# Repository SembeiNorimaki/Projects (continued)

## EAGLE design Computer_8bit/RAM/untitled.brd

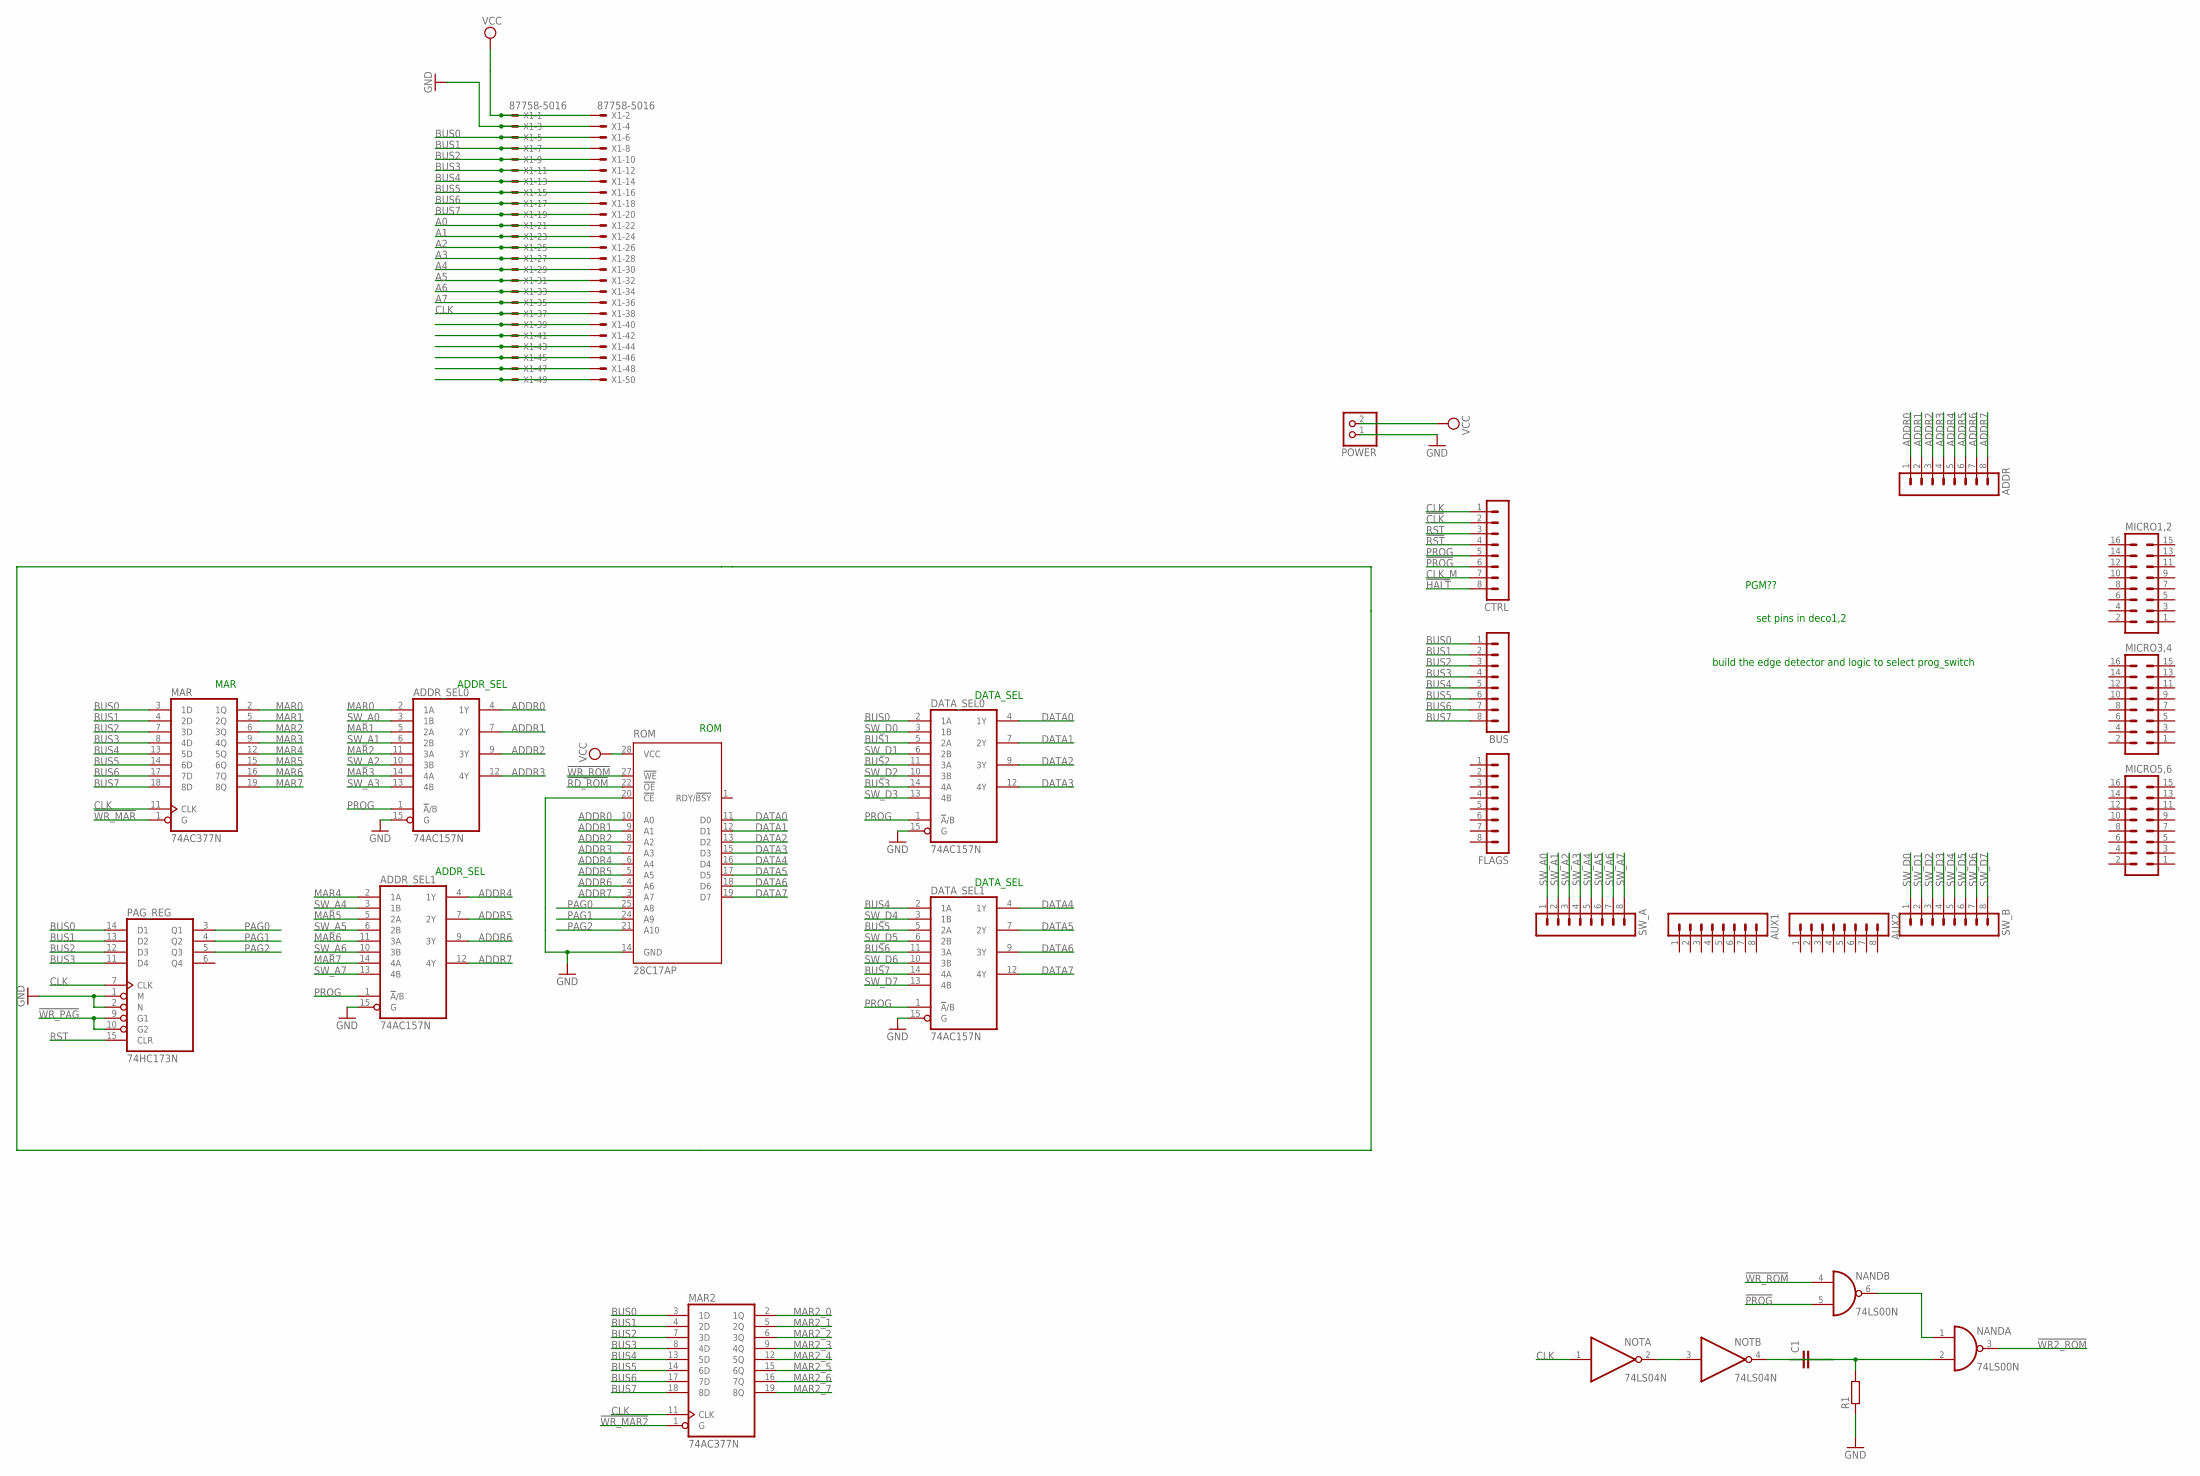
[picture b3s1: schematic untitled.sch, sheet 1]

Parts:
ADDR: MA08-1
ADDR_SEL0, ADDR_SEL1: 74AC157N; DIL16
AUX1, AUX2: MA08-1
BUS: MA08-1
C1: C2.5/4; C2.5-4
CTRL: MA08-1
DATA_SEL0, DATA_SEL1: 74AC157N; DIL16
FLAGS: MA08-1
MAR, MAR2: 74AC377N; DIL20
MICRO1,2, MICRO3,4, MICRO5,6: MA08-2
NAND: 74LS00N; DIL14
NOT: 74LS04N; DIL14
PAG_REG: 74HC173N; DIL16
POWER: PINHD-1X2; 1X02
R1: R0207/10; 0207/10
ROM: 28C17AP; DIL28-6
SW_A: MA08-1
SW_B: MA08-1
X1: 87758-5016

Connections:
!CLK: CTRL.2
!HALT: CTRL.8
!PROG: CTRL.6, NAND.5 (I1)
!RD_ROM: ROM.22 (!OE)
!RST: CTRL.4
!WR2_ROM: NAND.3 (O)
!WR_MAR: MAR.1 (G)
!WR_MAR2: MAR2.1 (G)
!WR_PAG: PAG_REG.9 (G1), PAG_REG.10 (G2)
!WR_ROM: NAND.4 (I0), ROM.27 (!WE)
A0: X1.21, X1.22
A1: X1.23, X1.24
A2: X1.25, X1.26
A3: X1.27, X1.28
A4: X1.29, X1.30
A5: X1.31, X1.32
A6: X1.33, X1.34
A7: X1.35, X1.36
ADDR0: ADDR.1, ADDR_SEL0.4 (1Y), ROM.10 (A0)
ADDR1: ADDR.2, ADDR_SEL0.7 (2Y), ROM.9 (A1)
ADDR2: ADDR.3, ADDR_SEL0.9 (3Y), ROM.8 (A2)
ADDR3: ADDR.4, ADDR_SEL0.12 (4Y), ROM.7 (A3)
ADDR4: ADDR.5, ADDR_SEL1.4 (1Y), ROM.6 (A4)
ADDR5: ADDR.6, ADDR_SEL1.7 (2Y), ROM.5 (A5)
ADDR6: ADDR.7, ADDR_SEL1.9 (3Y), ROM.4 (A6)
ADDR7: ADDR.8, ADDR_SEL1.12 (4Y), ROM.3 (A7)
BUS0: BUS.1, DATA_SEL0.2 (1A), MAR.3 (1D), MAR2.3 (1D), PAG_REG.14 (D1), X1.5, X1.6
BUS1: BUS.2, DATA_SEL0.5 (2A), MAR.4 (2D), MAR2.4 (2D), PAG_REG.13 (D2), X1.7, X1.8
BUS2: BUS.3, DATA_SEL0.11 (3A), MAR.7 (3D), MAR2.7 (3D), PAG_REG.12 (D3), X1.9, X1.10
BUS3: BUS.4, DATA_SEL0.14 (4A), MAR.8 (4D), MAR2.8 (4D), PAG_REG.11 (D4), X1.11, X1.12
BUS4: BUS.5, DATA_SEL1.2 (1A), MAR.13 (5D), MAR2.13 (5D), X1.13, X1.14
BUS5: BUS.6, DATA_SEL1.5 (2A), MAR.14 (6D), MAR2.14 (6D), X1.15, X1.16
BUS6: BUS.7, DATA_SEL1.11 (3A), MAR.17 (7D), MAR2.17 (7D), X1.17, X1.18
BUS7: BUS.8, DATA_SEL1.14 (4A), MAR.18 (8D), MAR2.18 (8D), X1.19, X1.20
CLK: CTRL.1, MAR.11 (CLK), MAR2.11 (CLK), NOT.1 (I), PAG_REG.7 (CLK), X1.37, X1.38
CLK_M: CTRL.7
DATA0: DATA_SEL0.4 (1Y), ROM.11 (D0)
DATA1: DATA_SEL0.7 (2Y), ROM.12 (D1)
DATA2: DATA_SEL0.9 (3Y), ROM.13 (D2)
DATA3: DATA_SEL0.12 (4Y), ROM.15 (D3)
DATA4: DATA_SEL1.4 (1Y), ROM.16 (D4)
DATA5: DATA_SEL1.7 (2Y), ROM.17 (D5)
DATA6: DATA_SEL1.9 (3Y), ROM.18 (D6)
DATA7: DATA_SEL1.12 (4Y), ROM.19 (D7)
GND: ADDR_SEL0.8 (GND), ADDR_SEL0.15 (G), ADDR_SEL1.8 (GND), ADDR_SEL1.15 (G), DATA_SEL0.8 (GND), DATA_SEL0.15 (G), DATA_SEL1.8 (GND), DATA_SEL1.15 (G), MAR.10 (GND), MAR2.10 (GND), NAND.7 (GND), NOT.7 (GND), PAG_REG.1 (M), PAG_REG.2 (N), PAG_REG.8 (GND), POWER.1, R1.1, ROM.14 (GND), ROM.20 (!CE), X1.3, X1.4
MAR0: ADDR_SEL0.2 (1A), MAR.2 (1Q)
MAR1: ADDR_SEL0.5 (2A), MAR.5 (2Q)
MAR2: ADDR_SEL0.11 (3A), MAR.6 (3Q)
MAR2_0: MAR2.2 (1Q)
MAR2_1: MAR2.5 (2Q)
MAR2_2: MAR2.6 (3Q)
MAR2_3: MAR2.9 (4Q)
MAR2_4: MAR2.12 (5Q)
MAR2_5: MAR2.15 (6Q)
MAR2_6: MAR2.16 (7Q)
MAR2_7: MAR2.19 (8Q)
MAR3: ADDR_SEL0.14 (4A), MAR.9 (4Q)
MAR4: ADDR_SEL1.2 (1A), MAR.12 (5Q)
MAR5: ADDR_SEL1.5 (2A), MAR.15 (6Q)
MAR6: ADDR_SEL1.11 (3A), MAR.16 (7Q)
MAR7: ADDR_SEL1.14 (4A), MAR.19 (8Q)
unnamed: X1.49, X1.50
unnamed: NOT.2 (O), NOT.3 (I)
unnamed: C1.2, NAND.2 (I1), R1.2
unnamed: C1.1, NOT.4 (O)
unnamed: NAND.1 (I0), NAND.6 (O)
unnamed: X1.39, X1.40
unnamed: X1.41, X1.42
unnamed: X1.43, X1.44
unnamed: X1.45, X1.46
unnamed: X1.47, X1.48
PAG0: PAG_REG.3 (Q1), ROM.25 (A8)
PAG1: PAG_REG.4 (Q2), ROM.24 (A9)
PAG2: PAG_REG.5 (Q3), ROM.21 (A10)
PROG: ADDR_SEL0.1 (!A!/B), ADDR_SEL1.1 (!A!/B), CTRL.5, DATA_SEL0.1 (!A!/B), DATA_SEL1.1 (!A!/B)
RST: CTRL.3, PAG_REG.15 (CLR)
SW_A0: ADDR_SEL0.3 (1B), SW_A.1
SW_A1: ADDR_SEL0.6 (2B), SW_A.2
SW_A2: ADDR_SEL0.10 (3B), SW_A.3
SW_A3: ADDR_SEL0.13 (4B), SW_A.4
SW_A4: ADDR_SEL1.3 (1B), SW_A.5
SW_A5: ADDR_SEL1.6 (2B), SW_A.6
SW_A6: ADDR_SEL1.10 (3B), SW_A.7
SW_A7: ADDR_SEL1.13 (4B), SW_A.8
SW_D0: DATA_SEL0.3 (1B), SW_B.1
SW_D1: DATA_SEL0.6 (2B), SW_B.2
SW_D2: DATA_SEL0.10 (3B), SW_B.3
SW_D3: DATA_SEL0.13 (4B), SW_B.4
SW_D4: DATA_SEL1.3 (1B), SW_B.5
SW_D5: DATA_SEL1.6 (2B), SW_B.6
SW_D6: DATA_SEL1.10 (3B), SW_B.7
SW_D7: DATA_SEL1.13 (4B), SW_B.8
VCC: ADDR_SEL0.16 (VCC), ADDR_SEL1.16 (VCC), DATA_SEL0.16 (VCC), DATA_SEL1.16 (VCC), MAR.20 (VCC), MAR2.20 (VCC), NAND.14 (VCC), NOT.14 (VCC), PAG_REG.16 (VCC), POWER.2, ROM.28 (VCC), X1.1, X1.2

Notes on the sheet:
ROM
MAR
ADDR_SEL
DATA_SEL
PGM??
set pins in deco1,2
build the edge detector and logic to select prog_switch

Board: 2 copper layers, 25 parts (0 on the bottom side), 77 nets, no tracks yet.

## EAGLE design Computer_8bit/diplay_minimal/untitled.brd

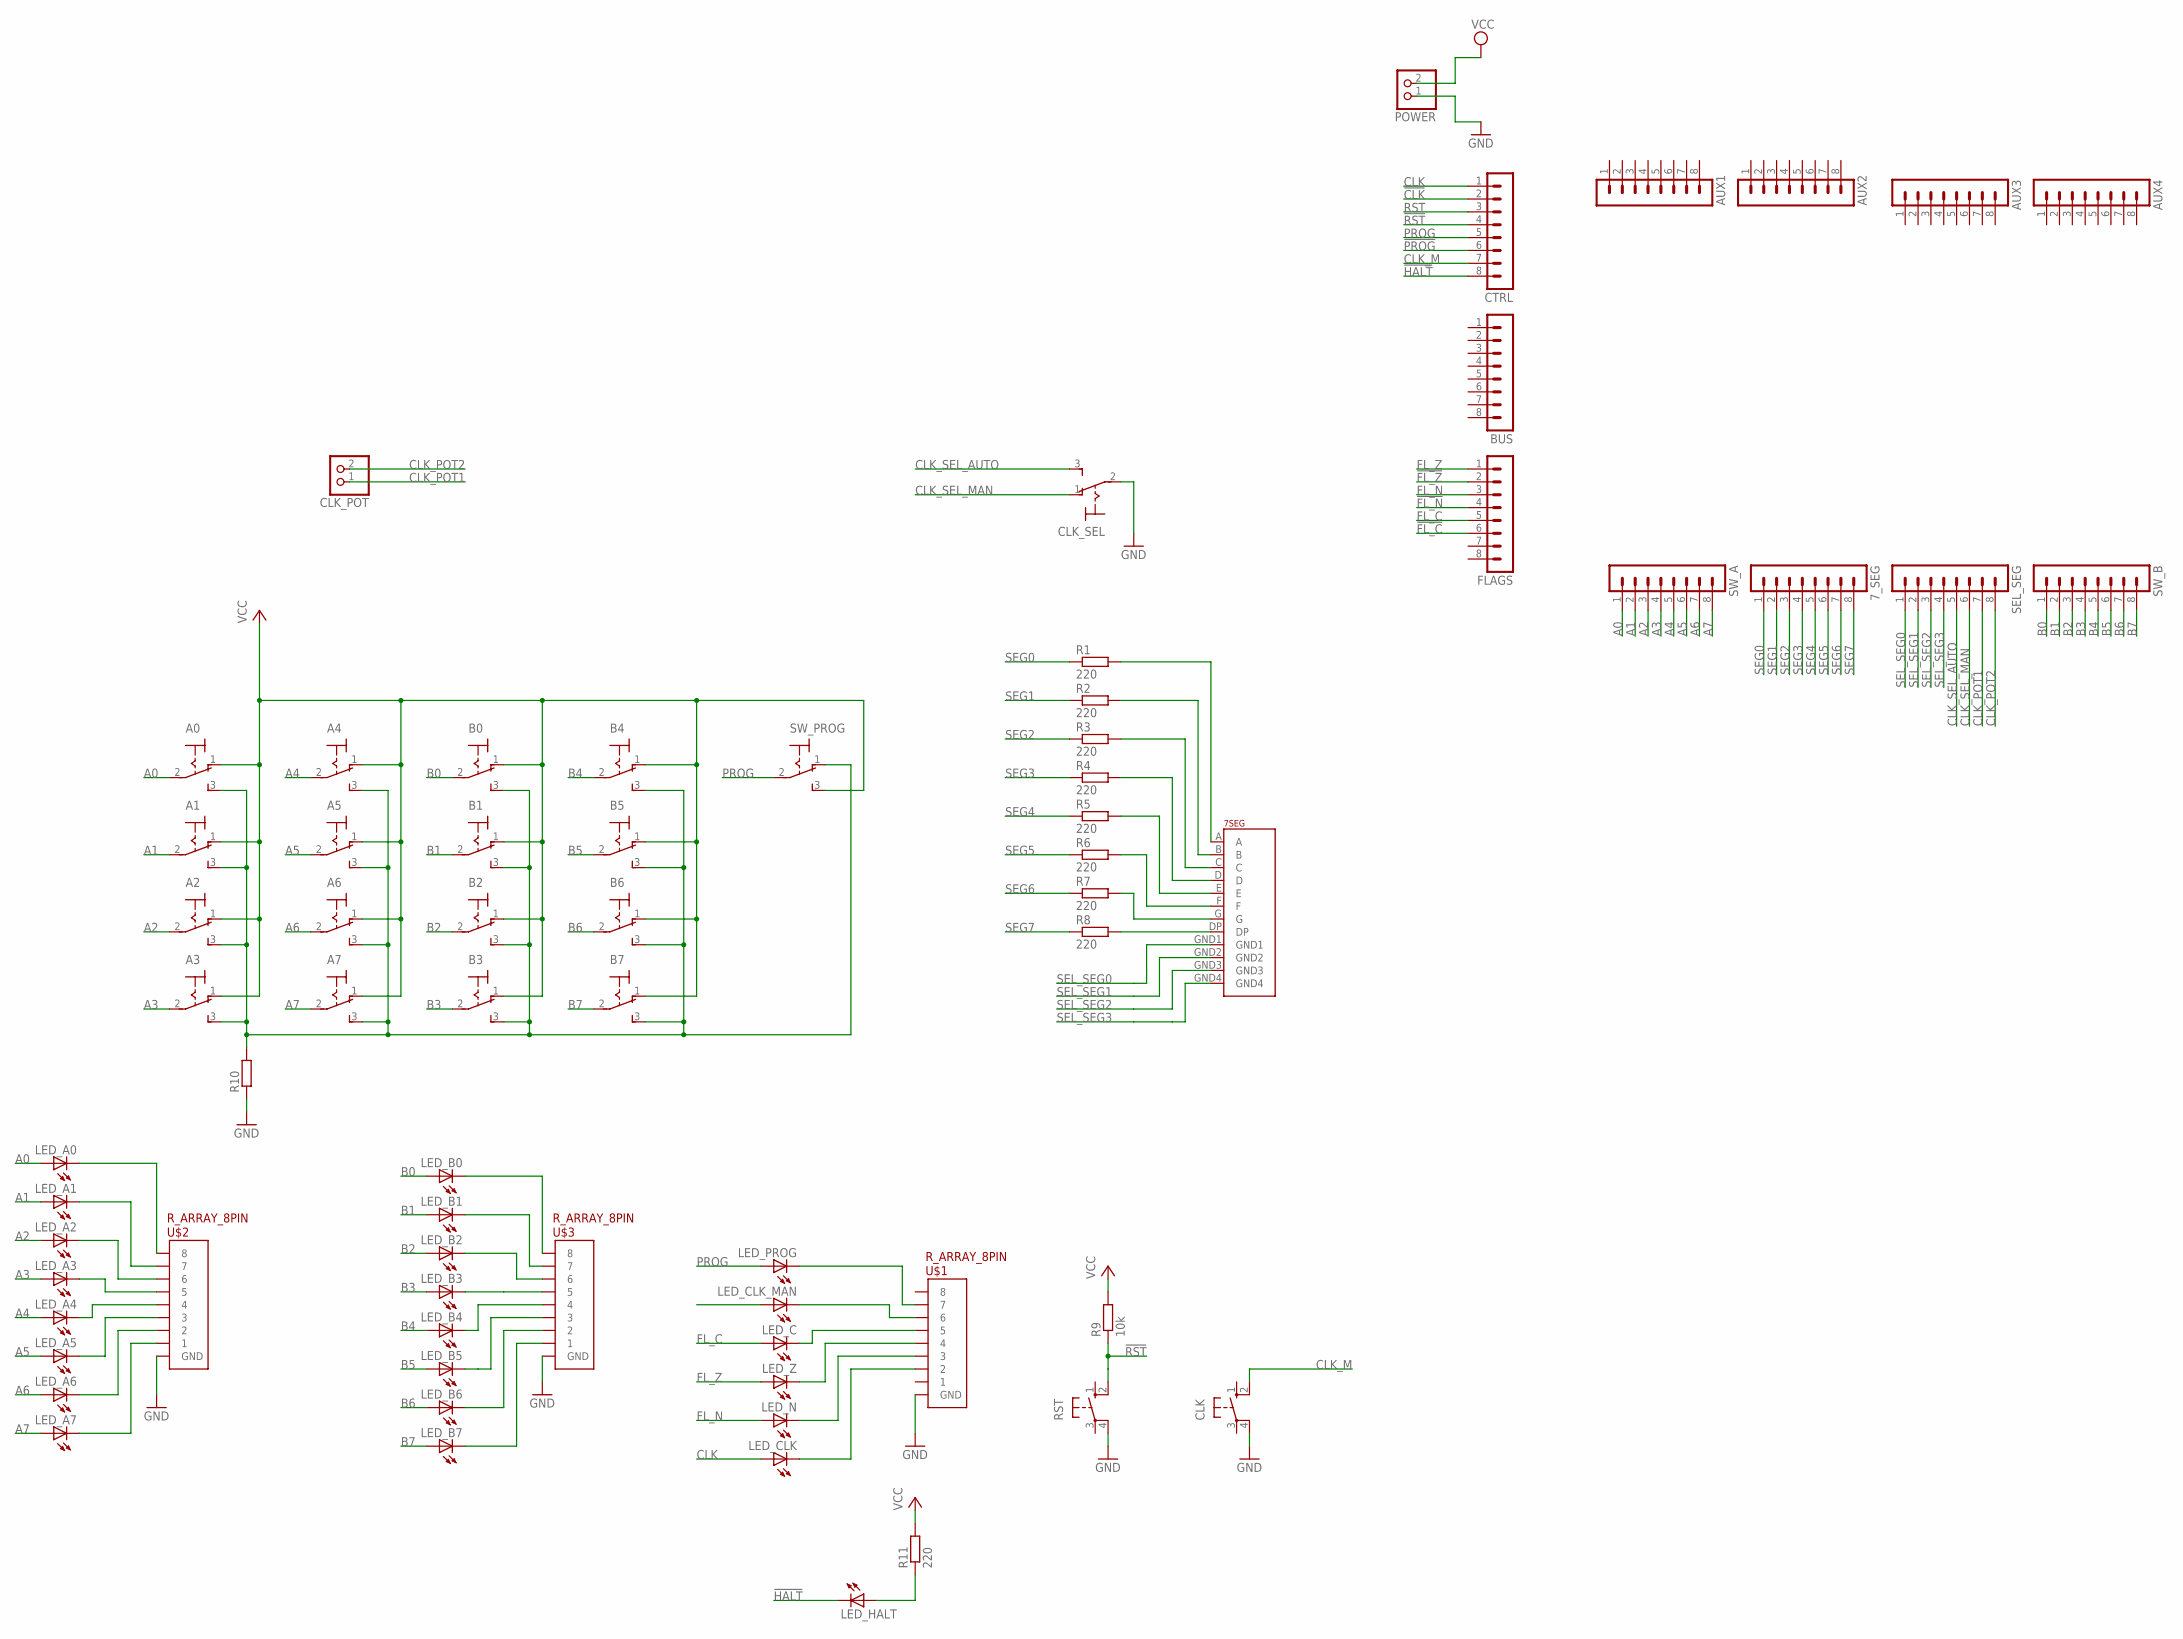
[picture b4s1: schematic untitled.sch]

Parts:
7SEG: 7SEGX4
7_SEG: MA08-1
A0, A1, A2, A3, A4, A5, A6, A7: M9040P
AUX1, AUX2, AUX3, AUX4: MA08-1
B0, B1, B2, B3, B4, B5, B6, B7: M9040P
BUS: MA08-1
CLK: 10-XX; B3F-10XX
CLK_POT: PINHD-1X2; 1X02
CLK_SEL: M9040P
CTRL: MA08-1
FLAGS: MA08-1
LED_A0, LED_A1, LED_A2, LED_A3, LED_A4, LED_A5, LED_A6, LED_A7: LED3MM
LED_B0, LED_B1, LED_B2, LED_B3, LED_B4, LED_B5, LED_B6, LED_B7: LED3MM
LED_C: LED3MM
LED_CLK: LED3MM
LED_CLK_MAN: LED3MM
LED_HALT: LED3MM
LED_N: LED3MM
LED_PROG: LED3MM
LED_Z: LED3MM
POWER: PINHD-1X2; 1X02
R1, R2, R3, R4, R5, R6, R7, R8, R11: 220; 0207/10
R9: 10k; 0207/10
R10: R0207/10; 0207/10
RST: 10-XX; B3F-10XX
SEL_SEG: MA08-1
SW_A: MA08-1
SW_B: MA08-1
SW_PROG: M9040P
U$1, U$2, U$3: R_ARRAY_8PIN

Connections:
!CLK: CTRL.2
!FL_C: FLAGS.6
!FL_N: FLAGS.4
!FL_Z: FLAGS.2
!HALT: CTRL.8, LED_HALT.K (C)
!PROG: CTRL.6
!RST: CTRL.4, R9.1, RST.2 (S1)
A0: A0.2, LED_A0.A, SW_A.1
A1: A1.2, LED_A1.A, SW_A.2
A2: A2.2, LED_A2.A, SW_A.3
A3: A3.2, LED_A3.A, SW_A.4
A4: A4.2, LED_A4.A, SW_A.5
A5: A5.2, LED_A5.A, SW_A.6
A6: A6.2, LED_A6.A, SW_A.7
A7: A7.2, LED_A7.A, SW_A.8
B0: B0.2, LED_B0.A, SW_B.1
B1: B1.2, LED_B1.A, SW_B.2
B2: B2.2, LED_B2.A, SW_B.3
B3: B3.2, LED_B3.A, SW_B.4
B4: B4.2, LED_B4.A, SW_B.5
B5: B5.2, LED_B5.A, SW_B.6
B6: B6.2, LED_B6.A, SW_B.7
B7: B7.2, LED_B7.A, SW_B.8
CLK: CTRL.1, LED_CLK.A
CLK_M: CLK.2 (S1), CTRL.7
CLK_POT1: CLK_POT.1, SEL_SEG.7
CLK_POT2: CLK_POT.2, SEL_SEG.8
CLK_SEL_AUTO: CLK_SEL.3 (S), SEL_SEG.5
CLK_SEL_MAN: CLK_SEL.1 (O), SEL_SEG.6
FL_C: FLAGS.5, LED_C.A
FL_N: FLAGS.3, LED_N.A
FL_Z: FLAGS.1, LED_Z.A
GND: CLK.4 (P1), CLK_SEL.2, POWER.1, R10.1, RST.4 (P1), U$1.GND, U$2.GND, U$3.GND
unnamed: LED_A0.K (C), U$2.8
unnamed: A0.3 (S), A1.3 (S), A2.3 (S), A3.3 (S), A4.3 (S), A5.3 (S), A6.3 (S), A7.3 (S), B0.3 (S), B1.3 (S), B2.3 (S), B3.3 (S), B4.3 (S), B5.3 (S), B6.3 (S), B7.3 (S), R10.2, SW_PROG.1 (O)
unnamed: 7SEG.A, R1.2
unnamed: LED_HALT.A, R11.1
unnamed: 7SEG.B, R2.2
unnamed: 7SEG.C, R3.2
unnamed: 7SEG.D, R4.2
unnamed: 7SEG.E, R5.2
unnamed: 7SEG.F, R6.2
unnamed: 7SEG.G, R7.2
unnamed: 7SEG.DP, R8.2
unnamed: LED_A1.K (C), U$2.7
unnamed: LED_A2.K (C), U$2.6
unnamed: LED_A3.K (C), U$2.5
unnamed: LED_A4.K (C), U$2.4
unnamed: LED_A5.K (C), U$2.3
unnamed: LED_A6.K (C), U$2.2
unnamed: LED_A7.K (C), U$2.1
unnamed: LED_B0.K (C), U$3.8
unnamed: LED_B1.K (C), U$3.7
unnamed: LED_B2.K (C), U$3.6
unnamed: LED_B3.K (C), U$3.5
unnamed: LED_B4.K (C), U$3.4
unnamed: LED_B5.K (C), U$3.3
unnamed: LED_B6.K (C), U$3.2
unnamed: LED_B7.K (C), U$3.1
unnamed: LED_PROG.K (C), U$1.7
unnamed: LED_CLK_MAN.K (C), U$1.6
unnamed: LED_C.K (C), U$1.5
unnamed: LED_Z.K (C), U$1.4
unnamed: LED_N.K (C), U$1.3
unnamed: LED_CLK.K (C), U$1.2
PROG: CTRL.5, LED_PROG.A, SW_PROG.2
RST: CTRL.3
SEG0: 7_SEG.1, R1.1
SEG1: 7_SEG.2, R2.1
SEG2: 7_SEG.3, R3.1
SEG3: 7_SEG.4, R4.1
SEG4: 7_SEG.5, R5.1
SEG5: 7_SEG.6, R6.1
SEG6: 7_SEG.7, R7.1
SEG7: 7_SEG.8, R8.1
SEL_SEG0: 7SEG.GND1, SEL_SEG.1
SEL_SEG1: 7SEG.GND2, SEL_SEG.2
SEL_SEG2: 7SEG.GND3, SEL_SEG.3
SEL_SEG3: 7SEG.GND4, SEL_SEG.4
VCC: A0.1 (O), A1.1 (O), A2.1 (O), A3.1 (O), A4.1 (O), A5.1 (O), A6.1 (O), A7.1 (O), B0.1 (O), B1.1 (O), B2.1 (O), B3.1 (O), B4.1 (O), B5.1 (O), B6.1 (O), B7.1 (O), POWER.2, R9.2, R11.2, SW_PROG.3 (S)

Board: 2 copper layers, 71 parts (0 on the bottom side), 74 nets, no tracks yet.

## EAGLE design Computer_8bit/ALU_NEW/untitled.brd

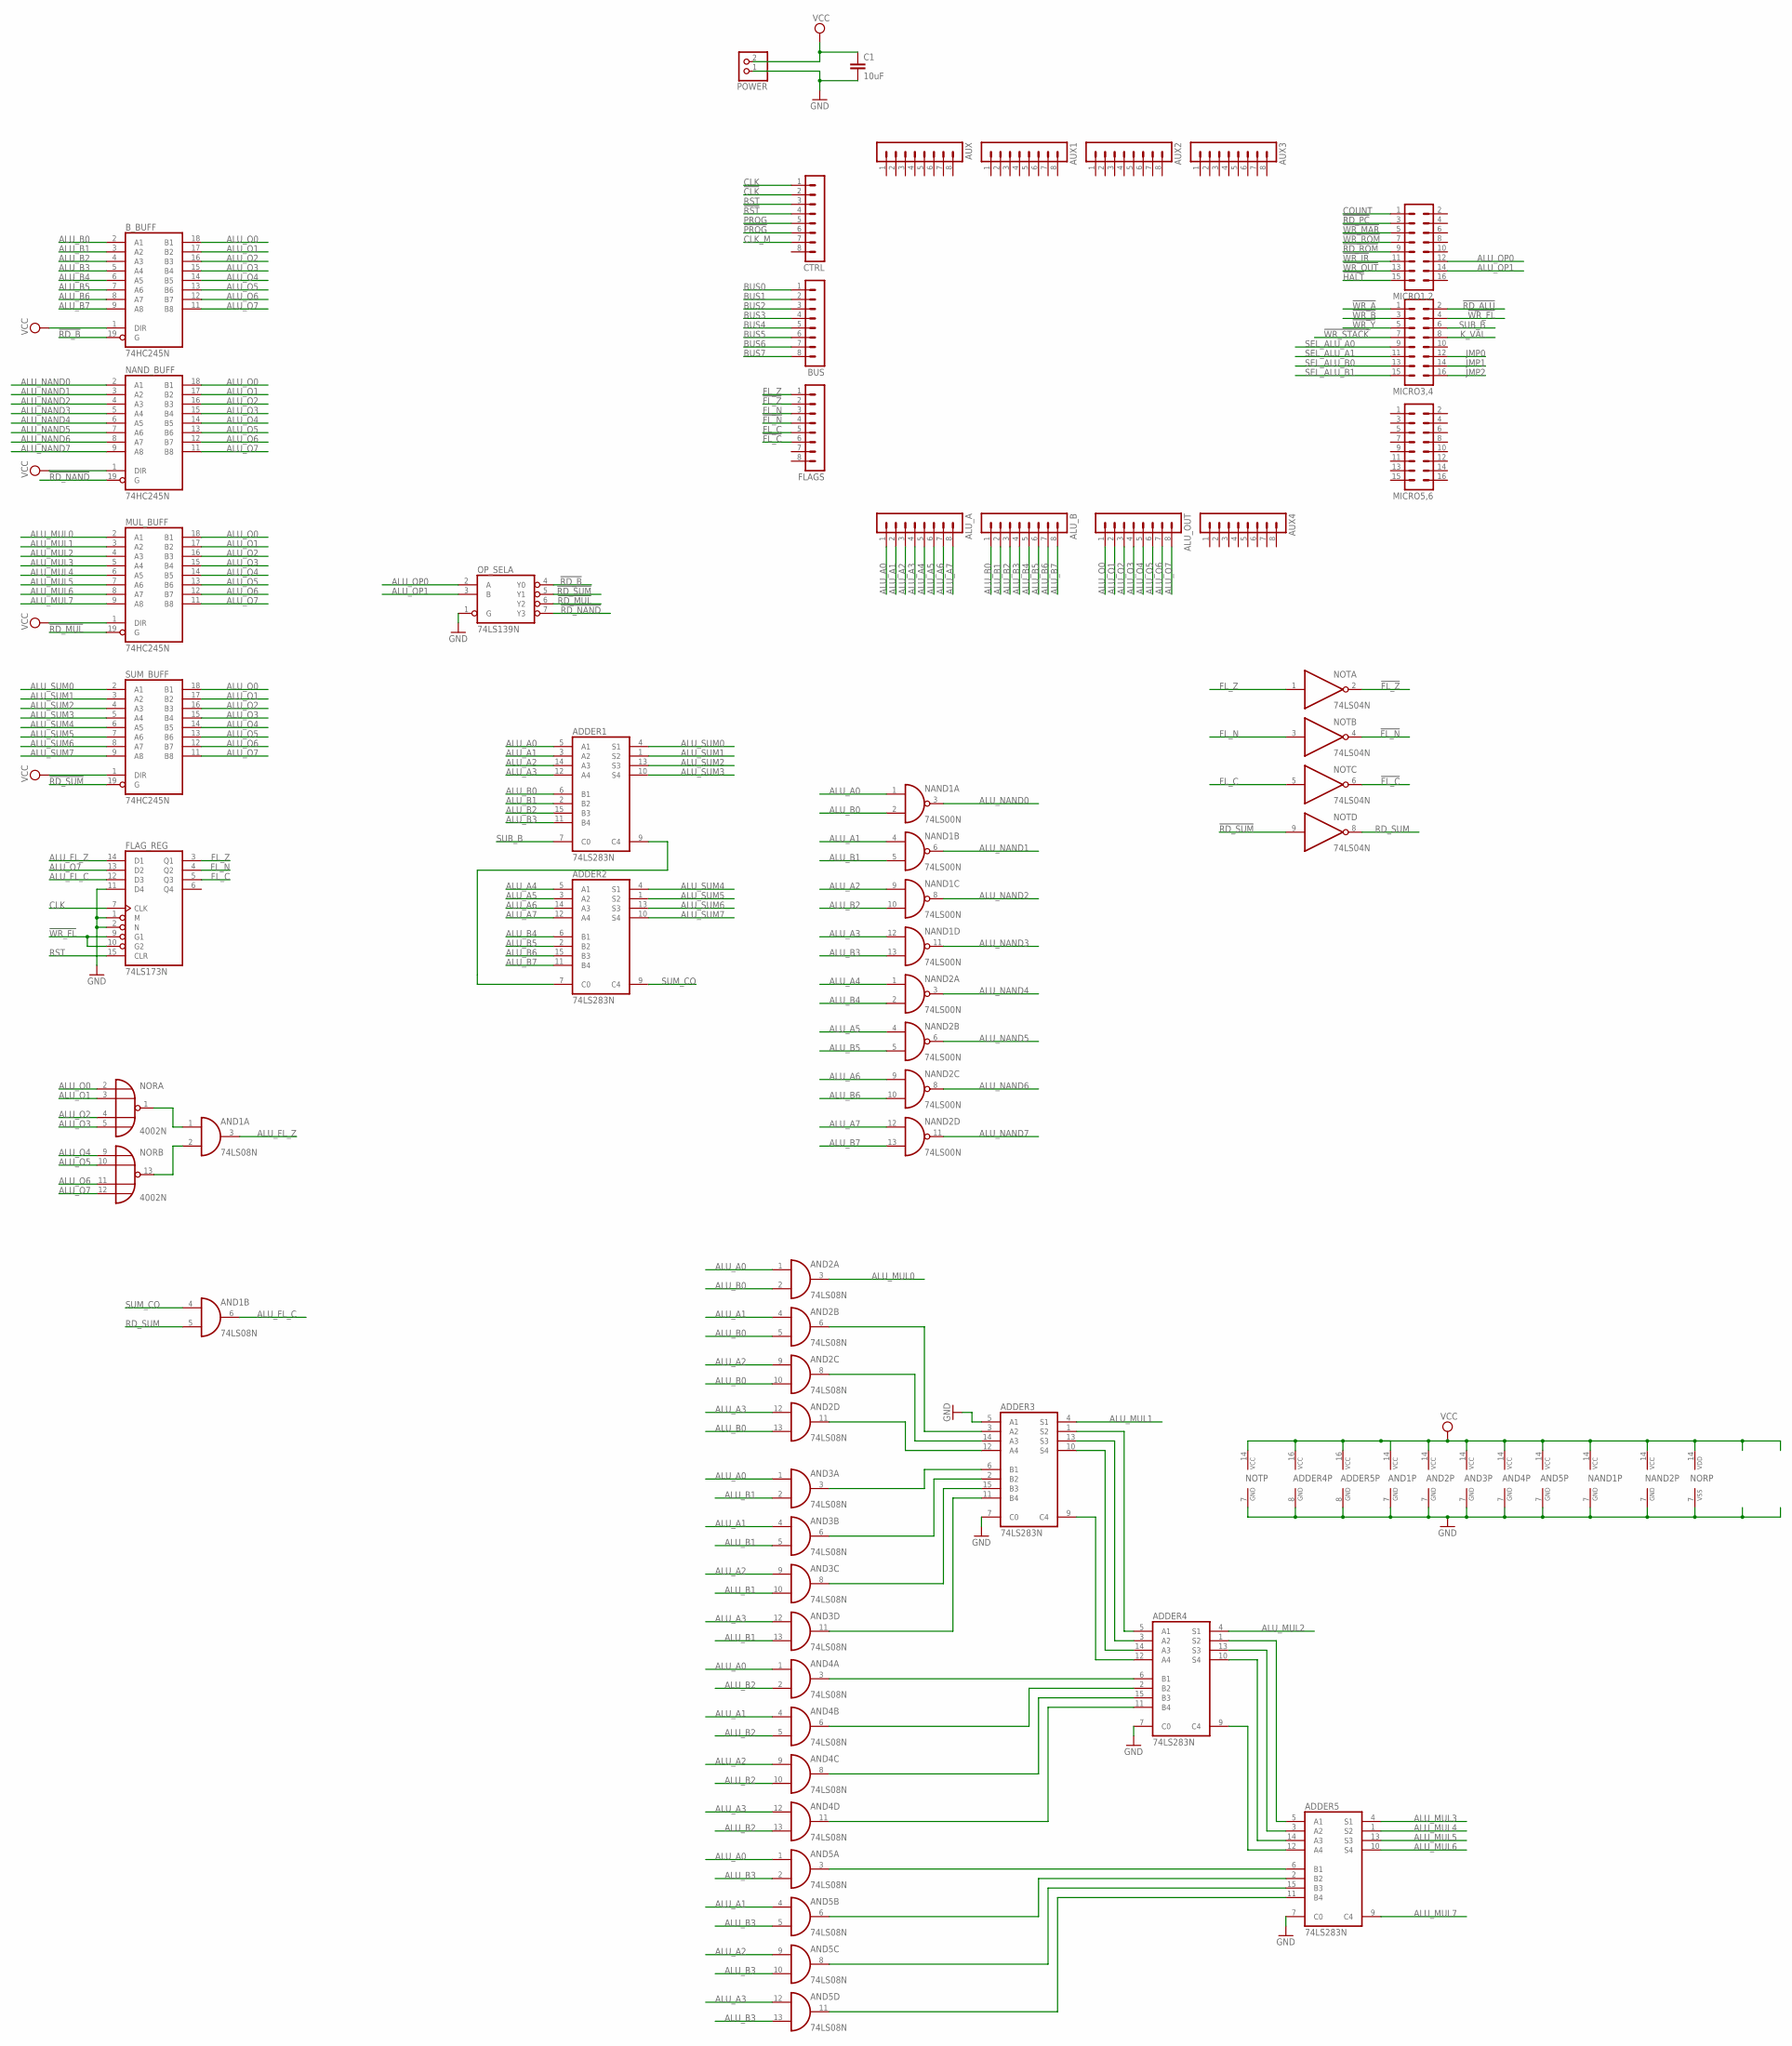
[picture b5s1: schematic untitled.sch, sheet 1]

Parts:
ADDER1, ADDER2, ADDER3, ADDER4, ADDER5: 74LS283N; DIL16
ALU_A: MA08-1
ALU_B: MA08-1
ALU_OUT: MA08-1
AND1, AND2, AND3, AND4, AND5: 74LS08N; DIL14
AUX, AUX1, AUX2, AUX3, AUX4: MA08-1
BUS: MA08-1
B_BUFF: 74HC245N; DIL20
C1: 10uF; C025-050X050
CTRL: MA08-1
FLAGS: MA08-1
FLAG_REG: 74LS173N; DIL16
MICRO1,2, MICRO3,4, MICRO5,6: MA08-2
MUL_BUFF: 74HC245N; DIL20
NAND1, NAND2: 74LS00N; DIL14
NAND_BUFF: 74HC245N; DIL20
NOR: 4002N; DIL14
NOT: 74LS04N; DIL14
OP_SEL: 74LS139N; DIL16
POWER: PINHD-1X2; 1X02
SUM_BUFF: 74HC245N; DIL20

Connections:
!CLK: CTRL.2
!FL_C: FLAGS.6, NOT.6 (O)
!FL_N: FLAGS.4, NOT.4 (O)
!FL_Z: FLAGS.2, NOT.2 (O)
!HALT: MICRO1,2.15
!PROG: CTRL.6
!RD_ALU: MICRO3,4.2
!RD_B: B_BUFF.19 (G), OP_SEL.4 (Y0)
!RD_MUL: MUL_BUFF.19 (G), OP_SEL.6 (Y2)
!RD_NAND: NAND_BUFF.19 (G), OP_SEL.7 (Y3)
!RD_PC: MICRO1,2.3
!RD_ROM: MICRO1,2.9
!RD_SUM: NOT.9 (I), OP_SEL.5 (Y1), SUM_BUFF.19 (G)
!RST: CTRL.4
!WR_A: MICRO3,4.1
!WR_B: MICRO3,4.3
!WR_FL: FLAG_REG.9 (G1), FLAG_REG.10 (G2), MICRO3,4.4
!WR_IR: MICRO1,2.11
!WR_MAR: MICRO1,2.5
!WR_OUT: MICRO1,2.13
!WR_ROM: MICRO1,2.7
!WR_STACK: MICRO3,4.7
!WR_Y: MICRO3,4.5
ALU_A0: ADDER1.5 (A1), ALU_A.1, AND2.1 (I0), AND3.1 (I0), AND4.1 (I0), AND5.1 (I0), NAND1.1 (I0)
ALU_A1: ADDER1.3 (A2), ALU_A.2, AND2.4 (I0), AND3.4 (I0), AND4.4 (I0), AND5.4 (I0), NAND1.4 (I0)
ALU_A2: ADDER1.14 (A3), ALU_A.3, AND2.9 (I0), AND3.9 (I0), AND4.9 (I0), AND5.9 (I0), NAND1.9 (I0)
ALU_A3: ADDER1.12 (A4), ALU_A.4, AND2.12 (I0), AND3.12 (I0), AND4.12 (I0), AND5.12 (I0), NAND1.12 (I0)
ALU_A4: ADDER2.5 (A1), ALU_A.5, NAND2.1 (I0)
ALU_A5: ADDER2.3 (A2), ALU_A.6, NAND2.4 (I0)
ALU_A6: ADDER2.14 (A3), ALU_A.7, NAND2.9 (I0)
ALU_A7: ADDER2.12 (A4), ALU_A.8, NAND2.12 (I0)
ALU_B0: ADDER1.6 (B1), ALU_B.1, AND2.2 (I1), AND2.5 (I1), AND2.10 (I1), AND2.13 (I1), B_BUFF.2 (A1), NAND1.2 (I1)
ALU_B1: ADDER1.2 (B2), ALU_B.2, AND3.2 (I1), AND3.5 (I1), AND3.10 (I1), AND3.13 (I1), B_BUFF.3 (A2), NAND1.5 (I1)
ALU_B2: ADDER1.15 (B3), ALU_B.3, AND4.2 (I1), AND4.5 (I1), AND4.10 (I1), AND4.13 (I1), B_BUFF.4 (A3), NAND1.10 (I1)
ALU_B3: ADDER1.11 (B4), ALU_B.4, AND5.2 (I1), AND5.5 (I1), AND5.10 (I1), AND5.13 (I1), B_BUFF.5 (A4), NAND1.13 (I1)
ALU_B4: ADDER2.6 (B1), ALU_B.5, B_BUFF.6 (A5), NAND2.2 (I1)
ALU_B5: ADDER2.2 (B2), ALU_B.6, B_BUFF.7 (A6), NAND2.5 (I1)
ALU_B6: ADDER2.15 (B3), ALU_B.7, B_BUFF.8 (A7), NAND2.10 (I1)
ALU_B7: ADDER2.11 (B4), ALU_B.8, B_BUFF.9 (A8), NAND2.13 (I1)
ALU_FL_C: AND1.6 (O), FLAG_REG.12 (D3)
ALU_FL_Z: AND1.3 (O), FLAG_REG.14 (D1)
ALU_MUL0: AND2.3 (O), MUL_BUFF.2 (A1)
ALU_MUL1: ADDER3.4 (S1), MUL_BUFF.3 (A2)
ALU_MUL2: ADDER4.4 (S1), MUL_BUFF.4 (A3)
ALU_MUL3: ADDER5.4 (S1), MUL_BUFF.5 (A4)
ALU_MUL4: ADDER5.1 (S2), MUL_BUFF.6 (A5)
ALU_MUL5: ADDER5.13 (S3), MUL_BUFF.7 (A6)
ALU_MUL6: ADDER5.10 (S4), MUL_BUFF.8 (A7)
ALU_MUL7: ADDER5.9 (C4), MUL_BUFF.9 (A8)
ALU_NAND0: NAND1.3 (O), NAND_BUFF.2 (A1)
ALU_NAND1: NAND1.6 (O), NAND_BUFF.3 (A2)
ALU_NAND2: NAND1.8 (O), NAND_BUFF.4 (A3)
ALU_NAND3: NAND1.11 (O), NAND_BUFF.5 (A4)
ALU_NAND4: NAND2.3 (O), NAND_BUFF.6 (A5)
ALU_NAND5: NAND2.6 (O), NAND_BUFF.7 (A6)
ALU_NAND6: NAND2.8 (O), NAND_BUFF.8 (A7)
ALU_NAND7: NAND2.11 (O), NAND_BUFF.9 (A8)
ALU_O0: ALU_OUT.1, B_BUFF.18 (B1), MUL_BUFF.18 (B1), NAND_BUFF.18 (B1), NOR.2 (I0), SUM_BUFF.18 (B1)
ALU_O1: ALU_OUT.2, B_BUFF.17 (B2), MUL_BUFF.17 (B2), NAND_BUFF.17 (B2), NOR.3 (I1), SUM_BUFF.17 (B2)
ALU_O2: ALU_OUT.3, B_BUFF.16 (B3), MUL_BUFF.16 (B3), NAND_BUFF.16 (B3), NOR.4 (I2), SUM_BUFF.16 (B3)
ALU_O3: ALU_OUT.4, B_BUFF.15 (B4), MUL_BUFF.15 (B4), NAND_BUFF.15 (B4), NOR.5 (I3), SUM_BUFF.15 (B4)
ALU_O4: ALU_OUT.5, B_BUFF.14 (B5), MUL_BUFF.14 (B5), NAND_BUFF.14 (B5), NOR.9 (I0), SUM_BUFF.14 (B5)
ALU_O5: ALU_OUT.6, B_BUFF.13 (B6), MUL_BUFF.13 (B6), NAND_BUFF.13 (B6), NOR.10 (I1), SUM_BUFF.13 (B6)
ALU_O6: ALU_OUT.7, B_BUFF.12 (B7), MUL_BUFF.12 (B7), NAND_BUFF.12 (B7), NOR.11 (I2), SUM_BUFF.12 (B7)
ALU_O7: ALU_OUT.8, B_BUFF.11 (B8), FLAG_REG.13 (D2), MUL_BUFF.11 (B8), NAND_BUFF.11 (B8), NOR.12 (I3), SUM_BUFF.11 (B8)
ALU_OP0: MICRO1,2.12, OP_SEL.2 (A)
ALU_OP1: MICRO1,2.14, OP_SEL.3 (B)
ALU_SUM0: ADDER1.4 (S1), SUM_BUFF.2 (A1)
ALU_SUM1: ADDER1.1 (S2), SUM_BUFF.3 (A2)
ALU_SUM2: ADDER1.13 (S3), SUM_BUFF.4 (A3)
ALU_SUM3: ADDER1.10 (S4), SUM_BUFF.5 (A4)
ALU_SUM4: ADDER2.4 (S1), SUM_BUFF.6 (A5)
ALU_SUM5: ADDER2.1 (S2), SUM_BUFF.7 (A6)
ALU_SUM6: ADDER2.13 (S3), SUM_BUFF.8 (A7)
ALU_SUM7: ADDER2.10 (S4), SUM_BUFF.9 (A8)
BUS0: BUS.1
BUS1: BUS.2
BUS2: BUS.3
BUS3: BUS.4
BUS4: BUS.5
BUS5: BUS.6
BUS6: BUS.7
BUS7: BUS.8
CLK: CTRL.1, FLAG_REG.7 (CLK)
CLK_M: CTRL.7
COUNT: MICRO1,2.1
FL_C: FLAGS.5, FLAG_REG.5 (Q3), NOT.5 (I)
FL_N: FLAGS.3, FLAG_REG.4 (Q2), NOT.3 (I)
FL_Z: FLAGS.1, FLAG_REG.3 (Q1), NOT.1 (I)
GND: ADDER1.8 (GND), ADDER2.8 (GND), ADDER3.5 (A1), ADDER3.7 (C0), ADDER3.8 (GND), ADDER4.7 (C0), ADDER4.8 (GND), ADDER5.7 (C0), ADDER5.8 (GND), AND1.7 (GND), AND2.7 (GND), AND3.7 (GND), AND4.7 (GND), AND5.7 (GND), B_BUFF.10 (GND), C1.2, FLAG_REG.1 (M), FLAG_REG.2 (N), FLAG_REG.8 (GND), FLAG_REG.11 (D4), MUL_BUFF.10 (GND), NAND1.7 (GND), NAND2.7 (GND), NAND_BUFF.10 (GND), NOR.7 (VSS), NOT.7 (GND), OP_SEL.1 (G), OP_SEL.8 (GND), POWER.1, SUM_BUFF.10 (GND)
JMP0: MICRO3,4.12
JMP1: MICRO3,4.14
JMP2: MICRO3,4.16
K_VAL: MICRO3,4.8
unnamed: ADDER3.11 (B4), AND3.11 (O)
unnamed: ADDER3.15 (B3), AND3.8 (O)
unnamed: ADDER3.2 (B2), AND3.6 (O)
unnamed: ADDER1.9 (C4), ADDER2.7 (C0)
unnamed: ADDER3.6 (B1), AND3.3 (O)
unnamed: ADDER3.12 (A4), AND2.11 (O)
unnamed: ADDER3.14 (A3), AND2.8 (O)
unnamed: ADDER3.3 (A2), AND2.6 (O)
unnamed: ADDER4.11 (B4), AND4.11 (O)
unnamed: ADDER4.15 (B3), AND4.8 (O)
unnamed: ADDER4.2 (B2), AND4.6 (O)
unnamed: ADDER4.6 (B1), AND4.3 (O)
unnamed: ADDER3.1 (S2), ADDER4.5 (A1)
unnamed: ADDER3.13 (S3), ADDER4.3 (A2)
unnamed: ADDER3.10 (S4), ADDER4.14 (A3)
unnamed: ADDER3.9 (C4), ADDER4.12 (A4)
unnamed: ADDER5.6 (B1), AND5.3 (O)
unnamed: ADDER5.2 (B2), AND5.6 (O)
unnamed: ADDER5.15 (B3), AND5.8 (O)
unnamed: ADDER5.11 (B4), AND5.11 (O)
unnamed: ADDER4.1 (S2), ADDER5.5 (A1)
unnamed: ADDER4.13 (S3), ADDER5.3 (A2)
unnamed: ADDER4.10 (S4), ADDER5.14 (A3)
unnamed: AND1.1 (I0), NOR.1 (O)
unnamed: AND1.2 (I1), NOR.13 (O)
unnamed: ADDER4.9 (C4), ADDER5.12 (A4)
PROG: CTRL.5
RD_SUM: AND1.5 (I1), NOT.8 (O)
RST: CTRL.3, FLAG_REG.15 (CLR)
SEL_ALU_A0: MICRO3,4.9
SEL_ALU_A1: MICRO3,4.11
SEL_ALU_B0: MICRO3,4.13
SEL_ALU_B1: MICRO3,4.15
SUB_B: ADDER1.7 (C0), MICRO3,4.6
SUM_CO: ADDER2.9 (C4), AND1.4 (I0)
VCC: ADDER1.16 (VCC), ADDER2.16 (VCC), ADDER3.16 (VCC), ADDER4.16 (VCC), ADDER5.16 (VCC), AND1.14 (VCC), AND2.14 (VCC), AND3.14 (VCC), AND4.14 (VCC), AND5.14 (VCC), B_BUFF.1 (DIR), B_BUFF.20 (VCC), C1.1, FLAG_REG.16 (VCC), MUL_BUFF.1 (DIR), MUL_BUFF.20 (VCC), NAND1.14 (VCC), NAND2.14 (VCC), NAND_BUFF.1 (DIR), NAND_BUFF.20 (VCC), NOR.14 (VDD), NOT.14 (VCC), OP_SEL.16 (VCC), POWER.2, SUM_BUFF.1 (DIR), SUM_BUFF.20 (VCC)

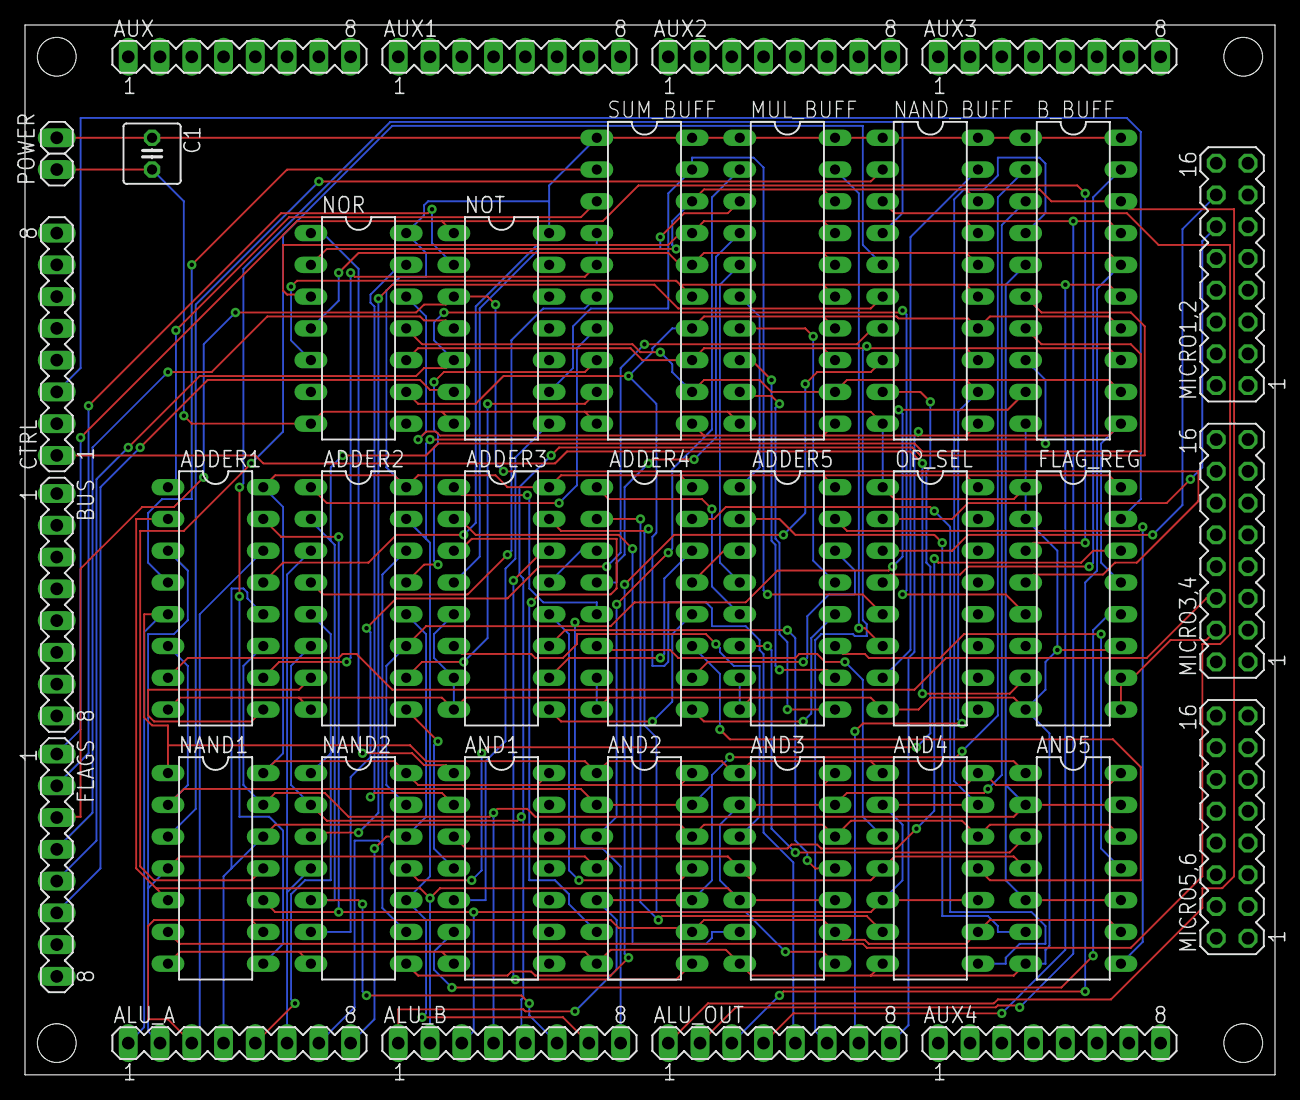
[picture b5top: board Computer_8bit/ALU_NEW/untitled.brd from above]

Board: 2 copper layers, 99.9 x 83.9 mm, 36 parts (0 on the bottom side), 96 nets.
